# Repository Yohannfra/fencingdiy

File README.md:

# FencingDIY

A collection of open source and free fencing devices and accessories.

## Goals

- Every plastic part must be 3D printable

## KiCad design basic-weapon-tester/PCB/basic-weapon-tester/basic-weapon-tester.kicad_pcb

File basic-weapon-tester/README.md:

# Basic weapon tester

This a very simple and cheap weapon tester for epee.

## Weapon compatibility

| Epee | Foil | Sabre |
| ---- | ---- | ----- |
| ✅    | ❌    | ❌     |

## 

## Required tools

- 3D printer

- Soldering iron

- Screwdriver (Phillips)

## Required components

| Name                        | Description

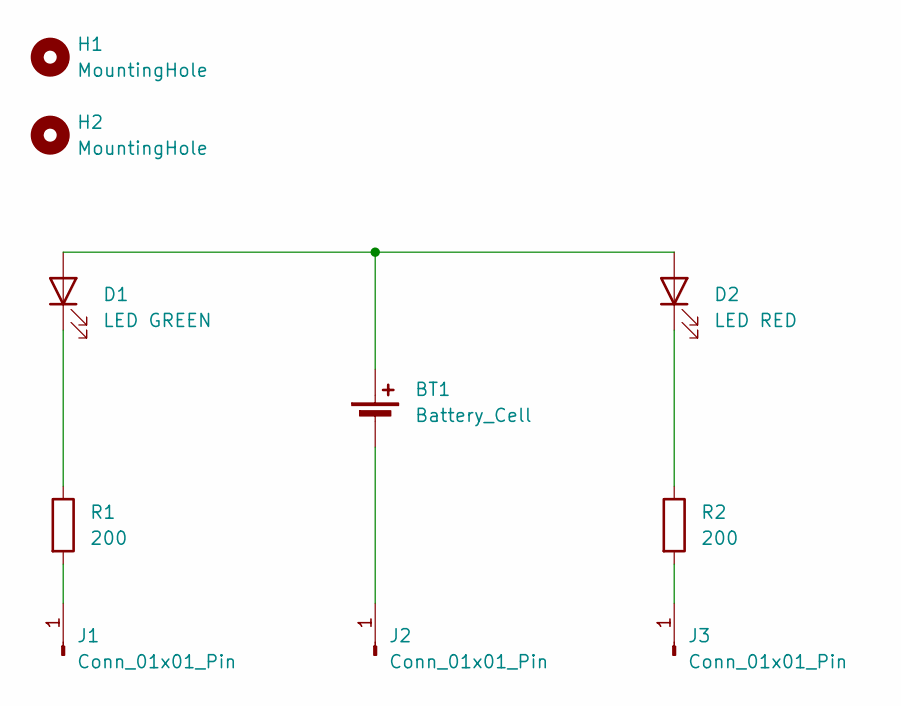
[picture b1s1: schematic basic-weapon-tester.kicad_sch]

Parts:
BT1: Battery_Cell; BatteryHolder_MYOUNG_BS-07-A1BJ001_CR2032
D1: LED GREEN; LED_D3.0mm
D2: LED RED; LED_D3.0mm
H1, H2: MountingHole; MountingHole_2.2mm_M2_DIN965
J1, J2, J3: Conn_01x01_Pin; PinHeader_1x01_P2.54mm_Vertical
R1, R2: 200; R_Axial_DIN0207_L6.3mm_D2.5mm_P10.16mm_Horizontal

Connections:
unnamed: BT1.1 (+), D1.2 (A), D2.2 (A)
unnamed: BT1.2 (-), J2.1 (Pin_1_1)
unnamed: D1.1 (K), R1.1
unnamed: D2.1 (K), R2.1
unnamed: J1.1 (Pin_1_1), R1.2
unnamed: J3.1 (Pin_1_1), R2.2

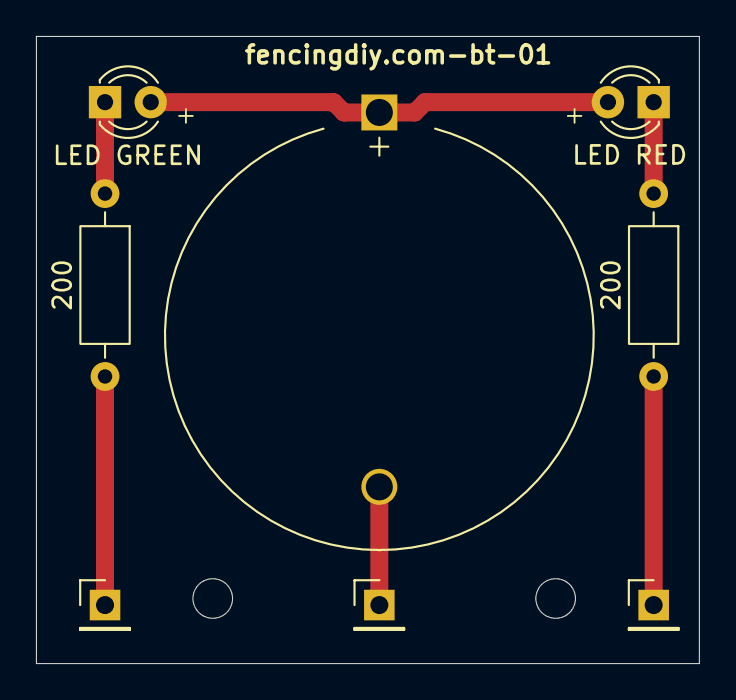
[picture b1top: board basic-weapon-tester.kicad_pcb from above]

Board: 2 copper layers, 36.8 x 34.8 mm, 11 parts (0 on the bottom side), 6 nets.

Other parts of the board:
H3: MountingHole; MountingHole_2.2mm_M2_DIN965

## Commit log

2026-06-18 create readme file
2026-06-18 add logo
2026-06-18 add astro template for site
2026-06-18 add github action to deploy website
2026-06-18 fix website url
2026-06-18 fix website url (2)
2026-06-18 fix website url (3)
2026-06-18 add logo variants
2026-06-18 improve website
2026-06-20 add basic-weapon-tester pcb + a few other small files
2026-06-22 intl website
2026-06-22 feat(website): add french locale
2026-06-22 doc(basic-weapon-tester): add compatibility chart and bom to readme
2026-06-22 fix(basic-weapon-tester/pcb): add missing drill files
